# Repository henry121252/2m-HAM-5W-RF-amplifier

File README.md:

# 5W RF amplifier for 2m HAM band

*V1.0 completed October 25th, 2026*

A 5W PA for transmitting on the 2m band, centered around the AFT05MS004NT1.

## Specifications

* **Transistor:** AFT05MS004NT1 LDMOS
* **Operating band:** 144-148MHz
* **Amplifier class:** AB
* **Quiescent bias:** 100mA
* **Input VSWR:** ~1.1 @ 146MHz
* **Input drive power:** ~15mW (+11.7 dBm)
* **Max power out:** ~5W (+37dBm) @ 146MHz
* **Power gain:** ~25dB @ 146MHz
* **Drain efficiency:** unmeasured
* **PCB:** 2-Layer custom PCB with embedded copper coin manufactured at home
* **Power supply:** LMR51420XDDCR buck converter w/ shielded inductor supplies 7.5V to the LDMOS drain with any Vin from +7.5V to +25V

## Architecture

* **Power stage:** The amplifier uses a single stage, common source Class AB topology built around the AFT05MS004NT1 LDMOS, biased at a quiescent drain current of 100mA from a 7.5V supply. An adjustable dc bias with thermal compensation is applied to the gate through a 1kΩ resistor. Drain power is fed through an RF choke of 220nH, bypassed with multi-value decoupling capacitors to present a low impedance RF ground across VHF and lower frequencies.
  
* **Impedance matching networks:** At 145MHz, the AFT05MS004NT1 datasheet specifies an optimal Zsource of 9.05+j12.43Ω to match its input impedance to 50Ω. This was done with a 47pF generator side shunt capacitor and a 24nH series inductor in an L-network. To match its output to 50Ω, the transistor requires a load impedance of 2.54-j0.54Ω. This results in a very large impedance transformation, and the resulting matching stage is very sensitive to component tolerances. I arrived at a pi-network design: 15pF generator shunt capacitor, 12nH series inductor, 100pF load side shunt capacitor. This matching networks also acts as a low pass filter, helping to reconstruct the original waveform of the input.

## Challenges

* **Amplifier stability:** Wideband RF LDMOS devices such as the AFT05MS004NT1 exhibit high gain well below their rated VHF/UHF operating range, making the transistor prone to self-oscillation. Good layout practice along with a 3.3Ω attenuator pad at the gate was used to prevent this oscillation.

* **Output matching:** Designing matching networks for a 2-layer homemade RF board was challenging because the AFT05MS004NT1 requires very low terminal impedances, notably the 2.5Ω load impedance at the drain represents roughly a 20:1 impedance transformation ratio to 50Ω. At VHF, even 1-2nH of unmodeled lead or trace inductance shifts the match noticeably. For fine tuning, values were refined by VNA measurements on a board with identical trace parasitics. A previous matching network had a much larger 330pF generator side shunt capacitor and, while numerically matched, the resulting RF output was only ~1.5W. The low 15pF generator side shunt capacitance stops high currents from travelling through the shunt and loading down the drain, resulting in the expected 5W output.

* **Input matching:** The input matching was tricky due to the rather long 50Ω trace leading into the matching network from the input port. Initial calculations were made for an L network with a source impedance of 9.05+j12.43Ω giving a generator side shunt capacitor of 39pF and a series inductor of 38nH. In practice, this network had an input VSWR of ~3.6 and required fine tuning. The final network of 47pF generator side shunt capacitor and 24nH series inductance gives an input VSWR of 1.124 at 146MHz.
  
* **Thermal interface:** Because the AFT05MS004NT1 dissipates up to 2.5W and comes in SOT-89, a very small SMD package, it requires the board to have a thermally conductive channel to dissipate heat. With a home made PCB, in-pad thermal vias are very difficult. Instead I modeled a rectangle underneath the source of the AFT05MS004NT1 to be cut out and replaced with a custom milled copper rectangle. The top and bottom of the copper was soldered to the ground plane, and the bottom solder is milled flat with the board to achieve an excellent thermal interface from the heatsink to the LDMOS. This process also results in quite a bit of solder on the front of the board.

* **Thermal compensation:** As the device claims to dissipate 2.5W at maximum output, I decided temperature compensation was necessary for the quiescent bias of the amplifier. As the temperature of the LDMOS goes up, its gate threshold voltage goes down. In the event that the transistor were to heat up, it would draw even more power and heat up more, thermal runaway. The AFT05MS004NT1's gate threshold voltage drops at approximately 2.2mV/°C. To achieve thermal compensation I summed my adjustable DC bias with the voltage drop of a BAS16W diode located on the same thermal interface as the LDMOS. The BAS16W diode drop decreases at about 1.9mV/°C, so the summing amplifier has 1.245x gain to bring that just above the negative temperature coefficient of the LDMOS gate.
  
* **Switching converter on an RF board:** Any RF amplifier needs a very solid, noise free power supply. Achieving this with a switching converter requires very careful layout and part selection to avoid interference with the RF components. Switching loops were made as small as possible and decoupling capacitors placed very tightly with good ground plane continuity. A shielded inductor was used to minimize radiated emissions from the converter. To minimize any remaining ripple on the supply, the +7.5V goes through a pi low pass filter, achieving ~40dB reduction in the fundamental switching frequency.

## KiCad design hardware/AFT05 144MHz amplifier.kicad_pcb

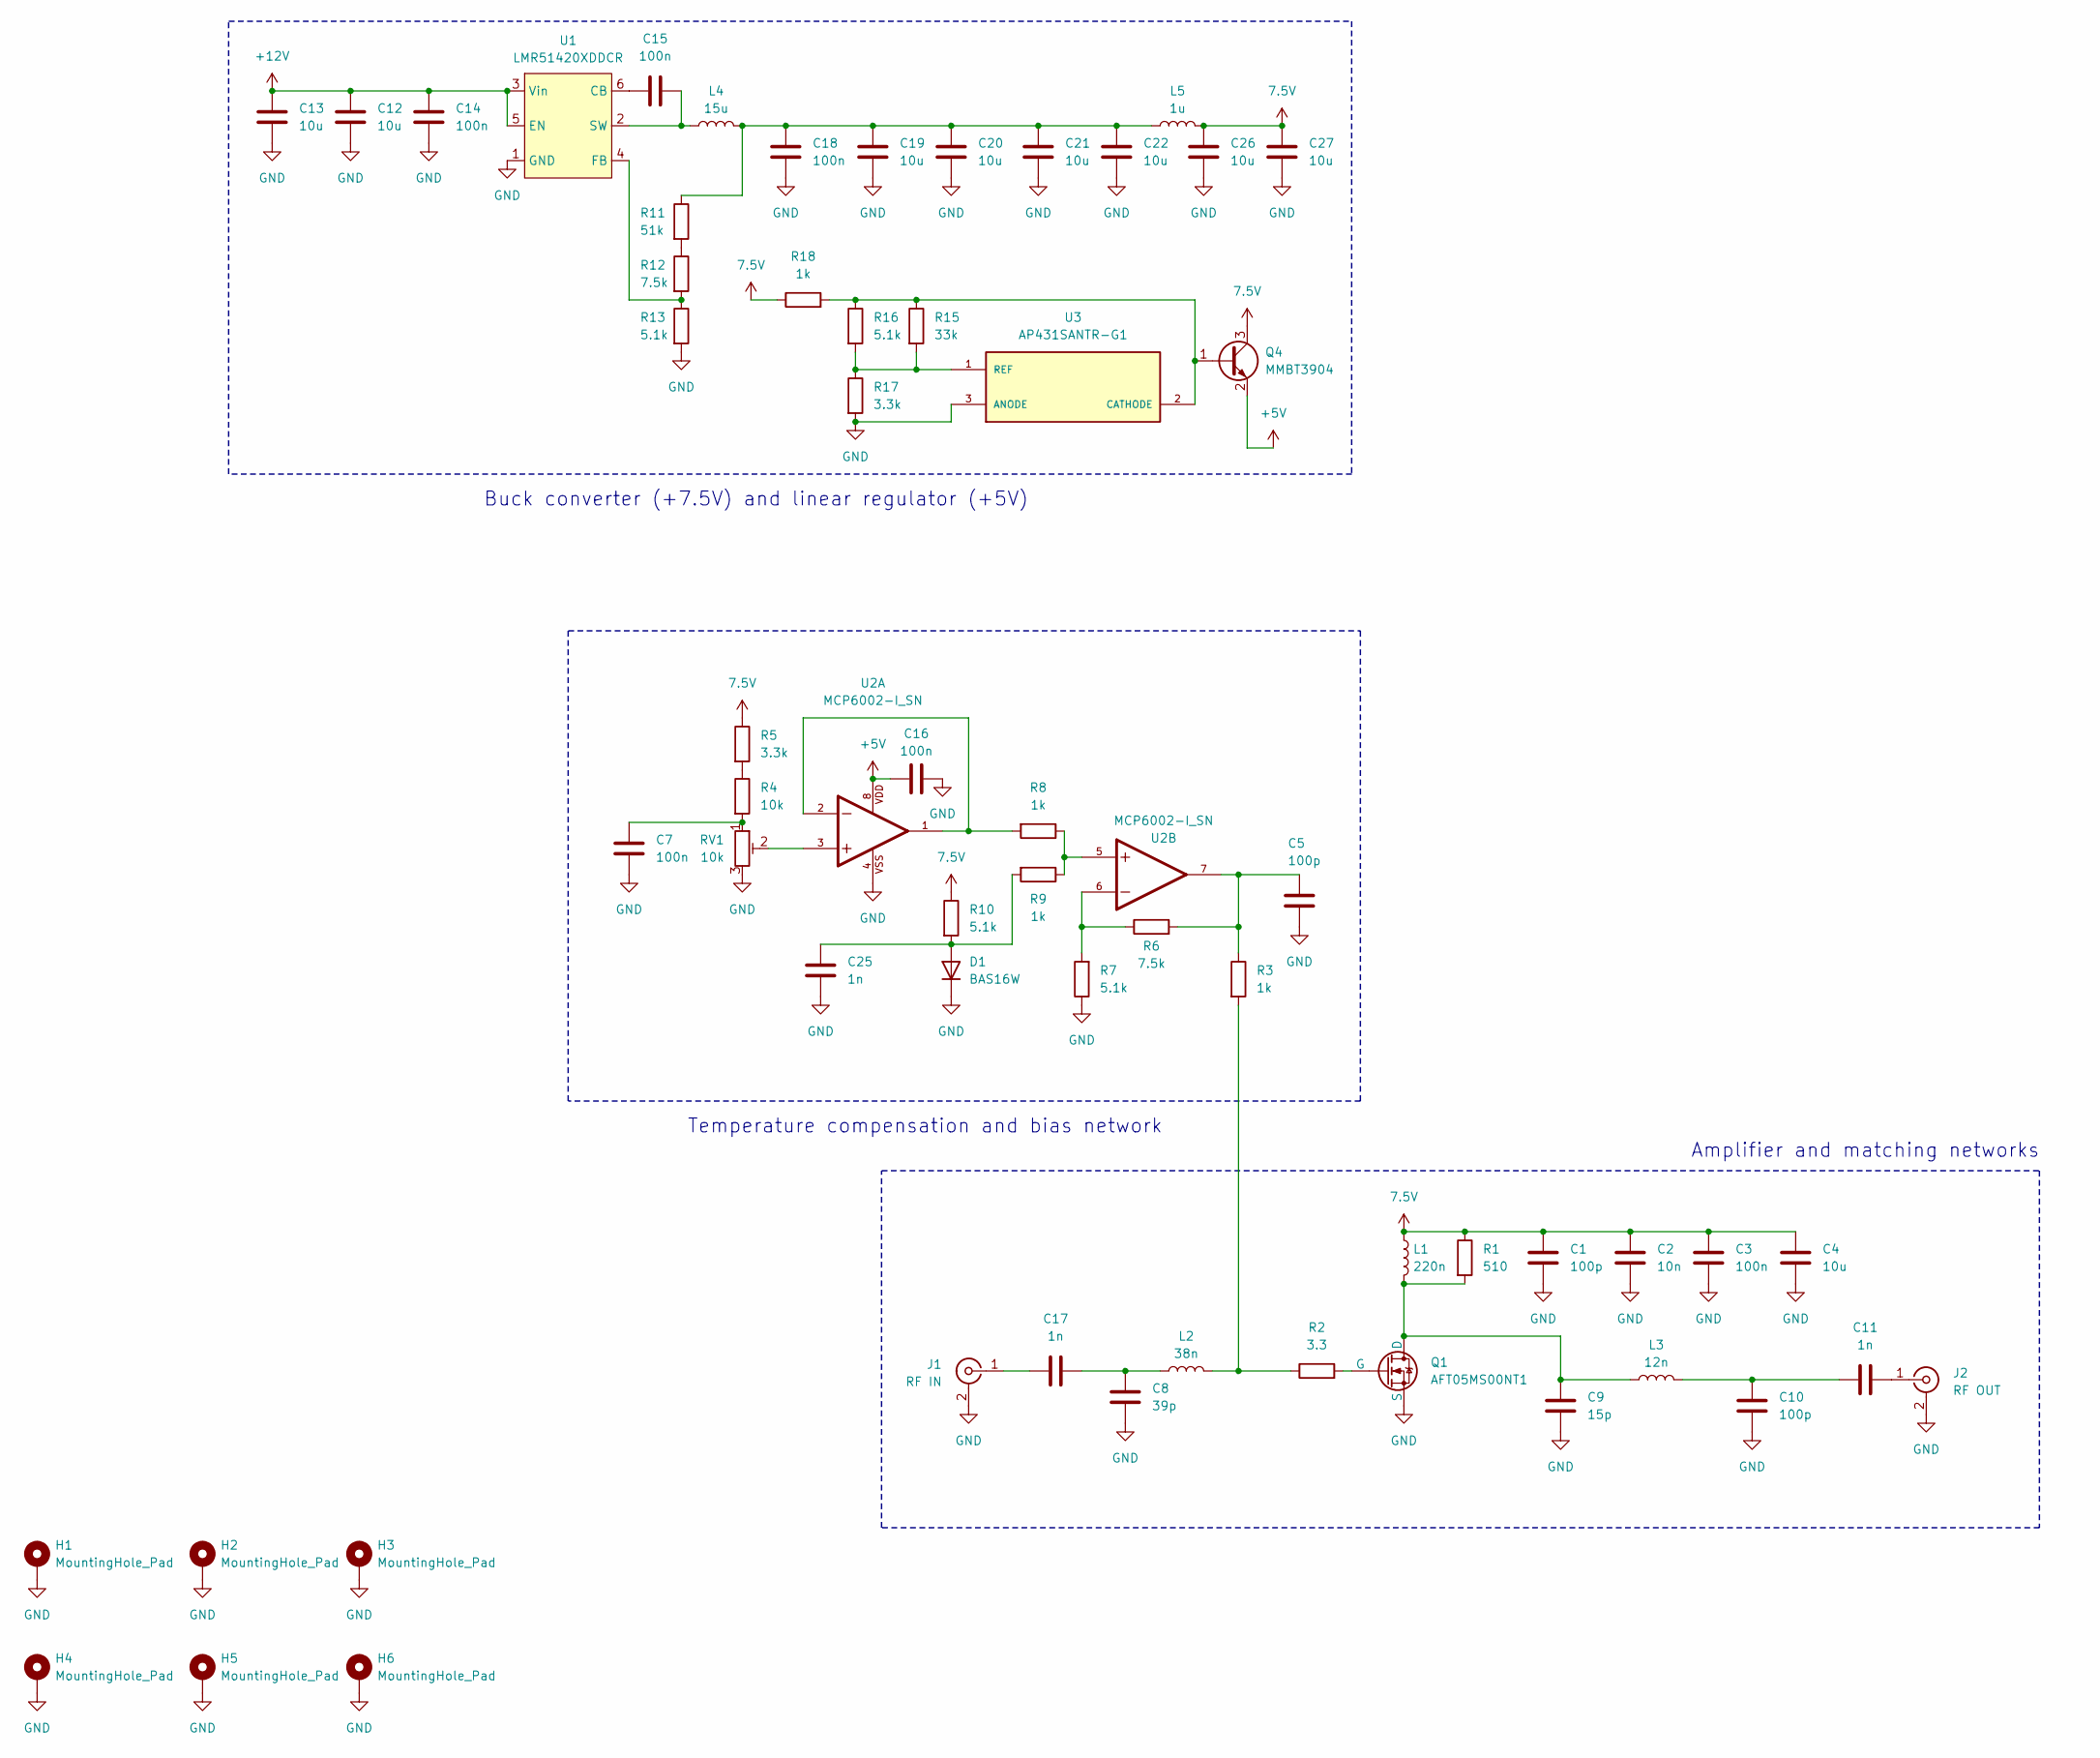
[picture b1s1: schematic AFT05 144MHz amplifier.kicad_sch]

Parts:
C1, C5: 100p; C_0603_1608Metric_Pad1.08x0.95mm_HandSolder
C2: 10n; C_0603_1608Metric_Pad1.08x0.95mm_HandSolder
C3, C7, C14, C15, C16, C18: 100n; C_0603_1608Metric_Pad1.08x0.95mm_HandSolder
C4, C12, C13, C19, C20, C21, C22, C26, C27: 10u; C_1206_3216Metric_Pad1.33x1.80mm_HandSolder
C8: 39p; C_0603_1608Metric_Pad1.08x0.95mm_HandSolder
C9: 15p; C_0805_2012Metric_Pad1.18x1.45mm_HandSolder
C10: 100p; C_0805_2012Metric_Pad1.18x1.45mm_HandSolder
C11: 1n; C_0805_2012Metric_Pad1.18x1.45mm_HandSolder
C17, C25: 1n; C_0603_1608Metric_Pad1.08x0.95mm_HandSolder
D1: BAS16W; SOT-323_SC-70
H1, H2, H3: MountingHole_Pad; MountingHole_2.2mm_M2
H4, H5, H6: MountingHole_Pad; MountingHole_3.2mm_M3
J1: RF IN; SMA_Amphenol_132289_EdgeMount
J2: RF OUT; SMA_Amphenol_132289_EdgeMount
L1: 220n; L 220nH 5.5mm diameter 8 turn 5.2mm length
L2: 38n; L 38nH 2.5mm diameter 6 turn 3.1mm length
L3: 12n; L 12nH 2.2mm diameter 3 turn 1.6mm length
L4: 15u; HCM1A0805V3-150-R
L5: 1u; 0806
Q1: AFT05MS00NT1; SOT-89-3
Q4: MMBT3904; SOT-23
R1: 510; R_0603_1608Metric_Pad0.98x0.95mm_HandSolder
R2: 3.3; R_0603_1608Metric_Pad0.98x0.95mm_HandSolder
R3, R8, R9, R18: 1k; R_0603_1608Metric_Pad0.98x0.95mm_HandSolder
R4: 10k; R_0603_1608Metric_Pad0.98x0.95mm_HandSolder
R5, R17: 3.3k; R_0603_1608Metric_Pad0.98x0.95mm_HandSolder
R6, R12: 7.5k; R_0603_1608Metric_Pad0.98x0.95mm_HandSolder
R7, R10, R13, R16: 5.1k; R_0603_1608Metric_Pad0.98x0.95mm_HandSolder
R11: 51k; R_0603_1608Metric_Pad0.98x0.95mm_HandSolder
R15: 33k; R_0603_1608Metric_Pad0.98x0.95mm_HandSolder
RV1: 10k; Potentiometer_Bourns_3224W_Vertical
U1: LMR51420XDDCR; SOT-23-6
U2: MCP6002-I_SN; MSOP-8_3x3mm_P0.65mm; PARTREV L
U3: AP431SANTR-G1; VREG_AP431SANTR-G1; PARTREV 1-2

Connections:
7.5V: C1.1, C2.1, C3.1, C4.1, C26.1, C27.1, L1.1, L5.2, Q4.3 (C), R1.1, R5.1, R10.1, R18.1
+5V: C16.1, Q4.2 (E), U2.8
+12V: C12.1, C13.1, C14.1, U1.3 (Vin), U1.5 (EN)
GND: C1.2, C2.2, C3.2, C4.2, C5.2, C7.2, C8.2, C9.2, C10.2, C12.2, C13.2, C14.2, C16.2, C18.2, C19.2, C20.2, C21.2, C22.2, C25.2, C26.2, C27.2, D1.3 (K), H1.1, H2.1, H3.1, H4.1, H5.1, H6.1, J1.2 (Ext), J2.2 (Ext), Q1.3 (S), R7.1, R13.2, R17.2, RV1.3, U1.1 (GND), U2.4, U3.3 (ANODE)
unnamed: C5.1, R3.1, R6.2, U2.7
unnamed: C7.1, R4.2, RV1.1
unnamed: C10.1, C11.1, L3.2
unnamed: C8.1, C17.2, L2.1
unnamed: C18.1, C19.1, C20.1, C21.1, C22.1, L4.2, L5.1, R11.1
unnamed: C25.1, D1.1 (A), R9.2, R10.2
unnamed: C17.1, J1.1 (In)
unnamed: C11.2, J2.1 (In)
unnamed: L2.2, R2.1, R3.2
unnamed: C9.1, L1.2, L3.1, Q1.1 (D), R1.2
unnamed: Q1.2 (G), R2.2
unnamed: Q4.1 (B), R15.1, R16.1, R18.2, U3.2 (CATHODE)
unnamed: R4.1, R5.2
unnamed: R6.1, R7.2, U2.6
unnamed: R8.1, R9.1, U2.5
unnamed: R8.2, U2.1, U2.2
unnamed: R11.2, R12.1
unnamed: RV1.2, U2.3
unnamed: C15.1, U1.6 (CB)
unnamed: R12.2, R13.1, U1.4 (FB)
unnamed: C15.2, L4.1, U1.2 (SW)
unnamed: R15.2, R16.2, R17.1, U3.1 (REF)

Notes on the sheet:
Temperature compensation and bias network
Amplifier and matching networks
Buck converter (+7.5V) and linear regulator (+5V)

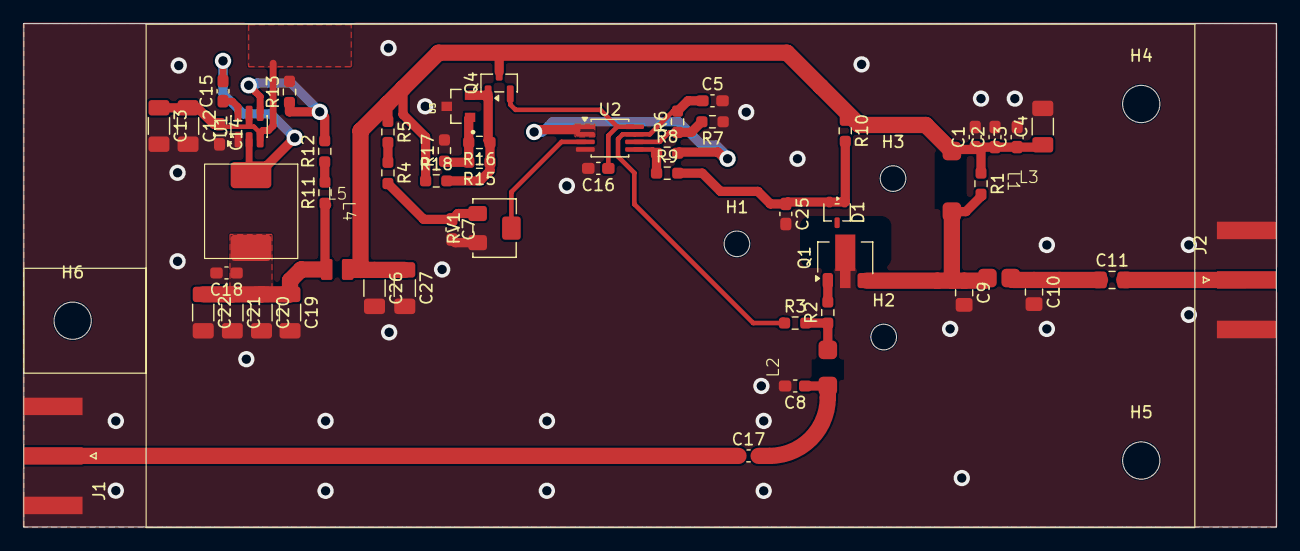
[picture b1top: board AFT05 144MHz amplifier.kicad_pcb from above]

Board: 2 copper layers, 107.5 x 43.2 mm, 61 parts (0 on the bottom side), 26 nets.
